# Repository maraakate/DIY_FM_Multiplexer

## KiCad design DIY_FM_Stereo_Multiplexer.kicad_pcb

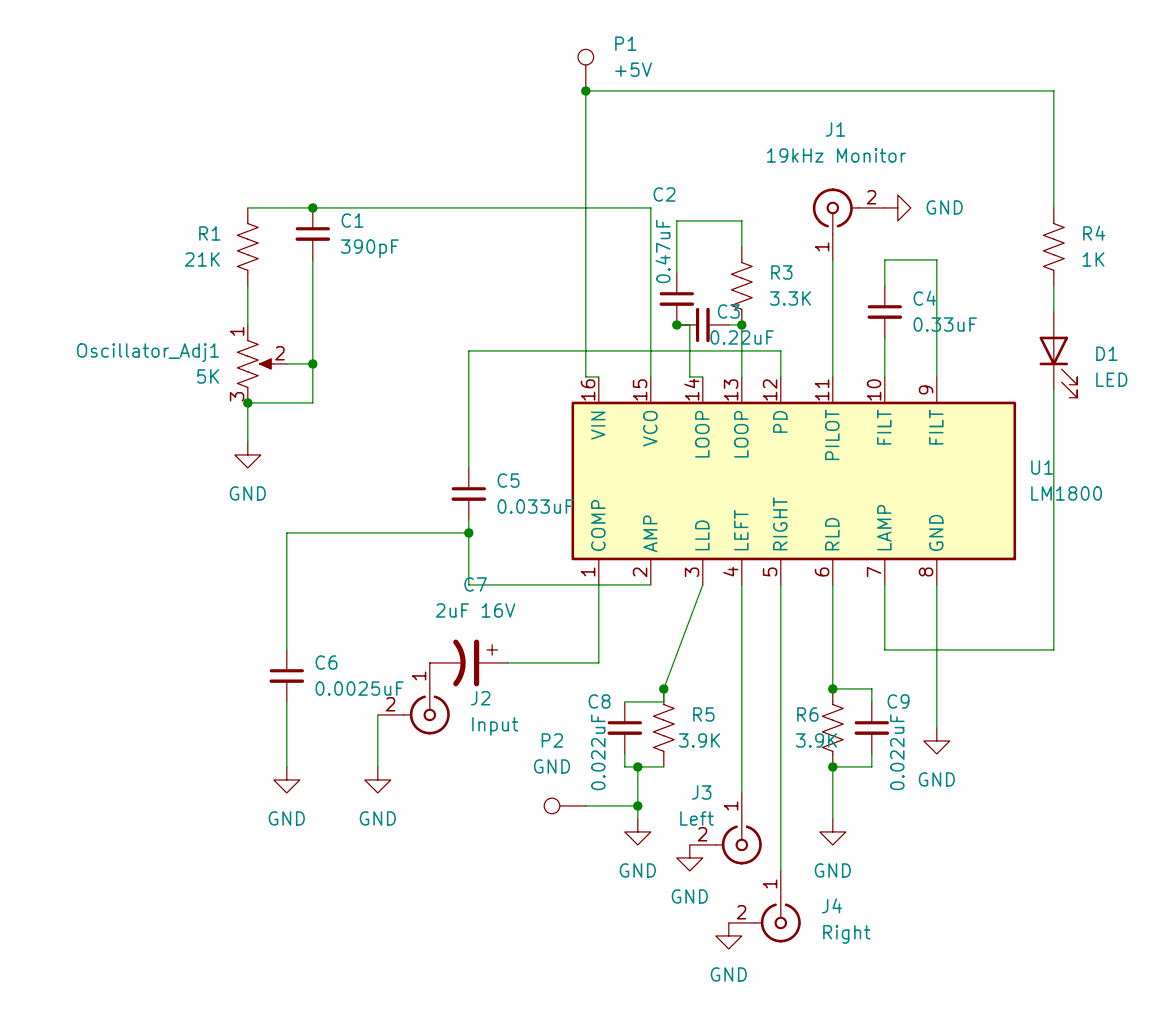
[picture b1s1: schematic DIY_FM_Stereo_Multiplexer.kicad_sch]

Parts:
C1: 390pF; C_Disc_D5.1mm_W3.2mm_P5.00mm
C2: 0.47uF; C_Disc_D5.1mm_W3.2mm_P5.00mm
C3: 0.22uF; C_Disc_D5.1mm_W3.2mm_P5.00mm
C4: 0.33uF; C_Disc_D5.1mm_W3.2mm_P5.00mm
C5: 0.033uF; C_Disc_D5.1mm_W3.2mm_P5.00mm
C6: 0.0025uF; C_Disc_D5.1mm_W3.2mm_P5.00mm
C7: 2uF 16V; C_Radial_D5.0mm_H11.0mm_P2.00mm
C8, C9: 0.022uF; C_Disc_D5.1mm_W3.2mm_P5.00mm
D1: LED; LED_D3.0mm
J1: 19kHz Monitor; SolderWire-0.127sqmm_1x02_P3.7mm_D0.48mm_OD1mm
J2: Input; SolderWire-0.127sqmm_1x02_P3.7mm_D0.48mm_OD1mm
J3: Left; SolderWire-0.127sqmm_1x02_P3.7mm_D0.48mm_OD1mm
J4: Right; SolderWire-0.127sqmm_1x02_P3.7mm_D0.48mm_OD1mm
Oscillator_Adj1: 5K; Potentiometer_Piher_PT-15-V15_Vertical
P1: +5V; TestPoint_THTPad_D3.0mm_Drill1.5mm
P2: GND; TestPoint_THTPad_D3.0mm_Drill1.5mm
R1: 21K; R_Axial_DIN0207_L6.3mm_D2.5mm_P10.16mm_Horizontal
R3: 3.3K; R_Axial_DIN0207_L6.3mm_D2.5mm_P10.16mm_Horizontal
R4: 1K; R_Axial_DIN0207_L6.3mm_D2.5mm_P10.16mm_Horizontal
R5, R6: 3.9K; R_Axial_DIN0207_L6.3mm_D2.5mm_P10.16mm_Horizontal
U1: LM1800; DIP-16_W7.62mm

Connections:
GND: C1.2, C6.2, C8.2, C9.2, J1.2 (Ext), J2.2 (Ext), J3.2 (Ext), J4.2 (Ext), Oscillator_Adj1.2, Oscillator_Adj1.3, P2.1, R5.2, R6.2, U1.8 (GND)
unnamed: C2.1, R3.1
unnamed: C2.2, C3.1, U1.14 (LOOP)
unnamed: C7.2, J2.1 (In)
unnamed: Oscillator_Adj1.1, R1.2
unnamed: P1.1, R4.1, U1.16 (VIN)
unnamed: D1.2 (A), R4.2
unnamed: C7.1, U1.1 (COMP)
unnamed: C5.2, C6.1, U1.2 (AMP)
unnamed: C8.1, R5.1, U1.3 (LLD)
unnamed: J3.1 (In), U1.4 (LEFT)
unnamed: J4.1 (In), U1.5 (RIGHT)
unnamed: C9.1, R6.1, U1.6 (RLD)
unnamed: D1.1 (K), U1.7 (LAMP)
unnamed: C4.1, U1.9 (FILT)
unnamed: C4.2, U1.10 (FILT)
unnamed: J1.1 (In), U1.11 (PILOT)
unnamed: C5.1, U1.12 (PD)
unnamed: C3.2, R3.2, U1.13 (LOOP)
unnamed: C1.1, R1.1, U1.15 (VCO)

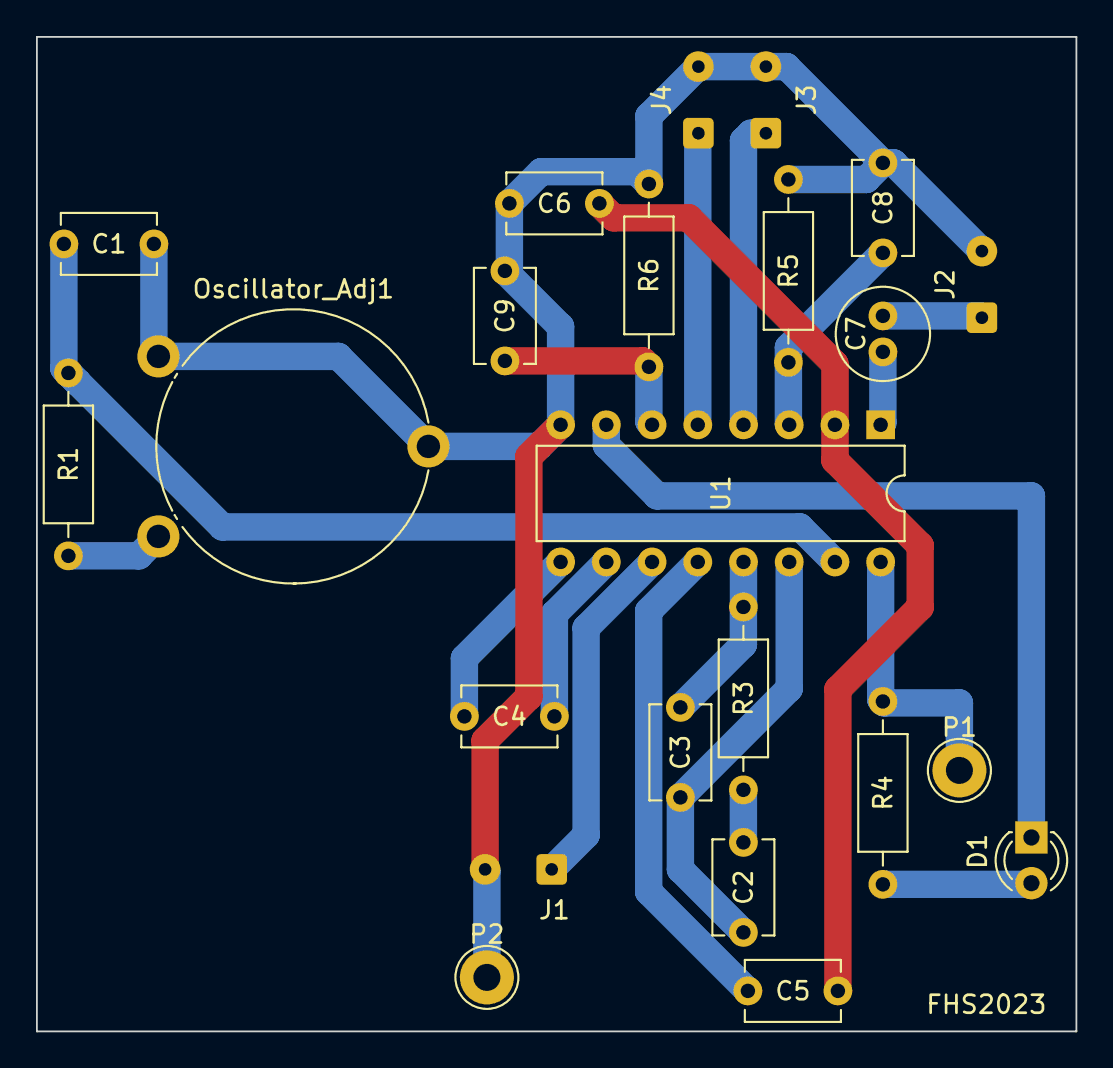
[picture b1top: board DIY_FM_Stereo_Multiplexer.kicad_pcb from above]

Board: 2 copper layers, 57.8 x 55.2 mm, 23 parts (0 on the bottom side), 20 nets.
